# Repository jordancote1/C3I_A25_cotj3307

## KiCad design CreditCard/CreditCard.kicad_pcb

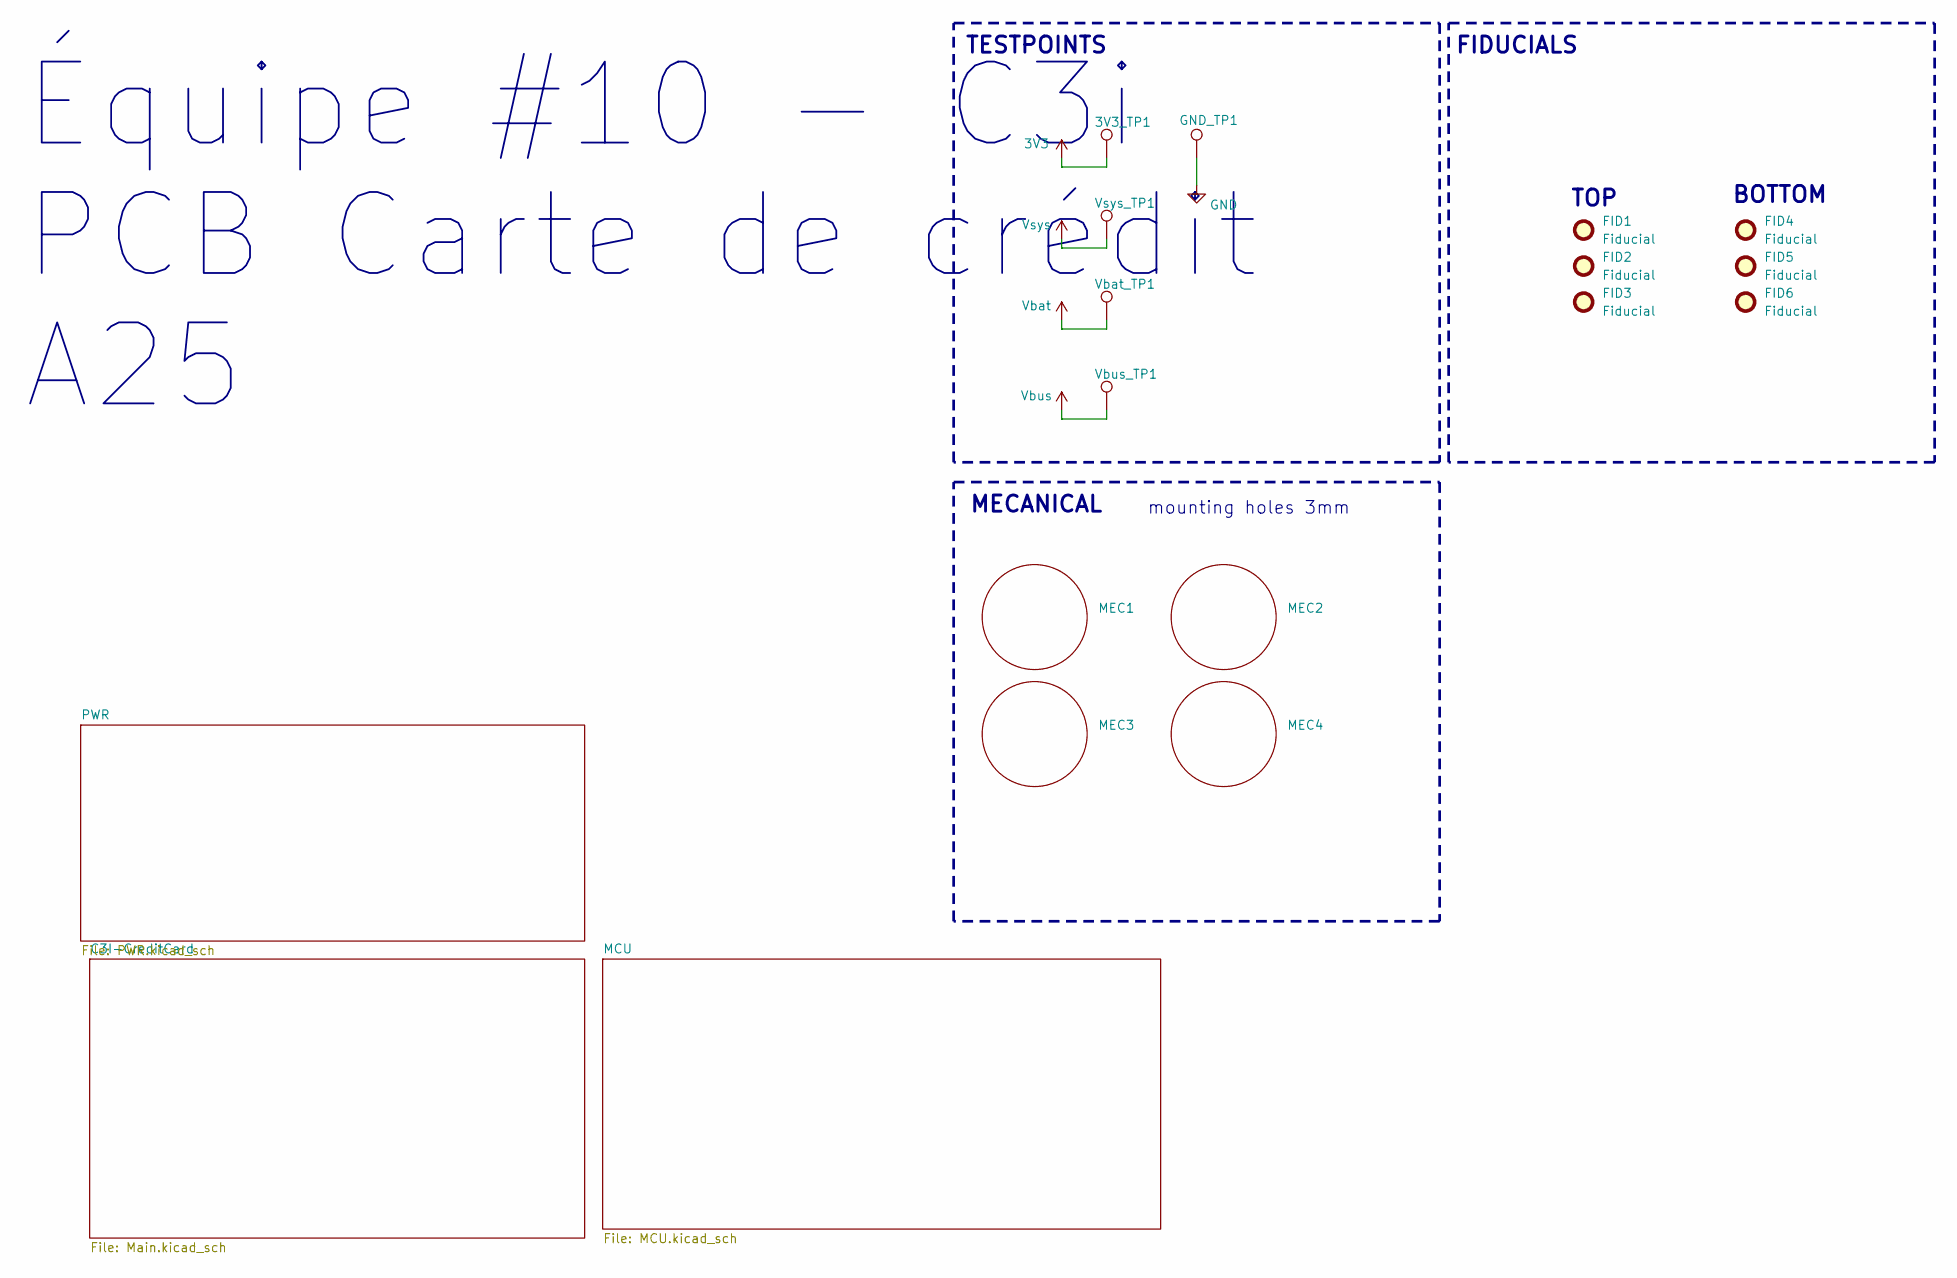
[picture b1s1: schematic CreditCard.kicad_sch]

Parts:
3V3_TP1: TP; TestPoint_Pad_D1.5mm
FID1, FID2, FID3, FID4, FID5, FID6: Fiducial; Fiducial_0.5mm_Mask1.5mm
GND_TP1: TP; TestPoint_Pad_D1.5mm
MEC1, MEC2, MEC3, MEC4: Mounting_3mm
Vbat_TP1: TP; TestPoint_Pad_D1.5mm
Vbus_TP1: TP; TestPoint_Pad_D1.5mm
Vsys_TP1: TP; TestPoint_Pad_D1.5mm

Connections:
3V3: 3V3_TP1.1; also elsewhere on the board
GND: GND_TP1.1; also elsewhere on the board
Vbat: Vbat_TP1.1; also elsewhere on the board
Vbus: Vbus_TP1.1; also elsewhere on the board
Vsys: Vsys_TP1.1; also elsewhere on the board

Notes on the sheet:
Équipe #10 - C3i PCB Carte de crédit A25
BOTTOM
MECANICAL
TESTPOINTS
FIDUCIALS
TOP
mounting holes 3mm

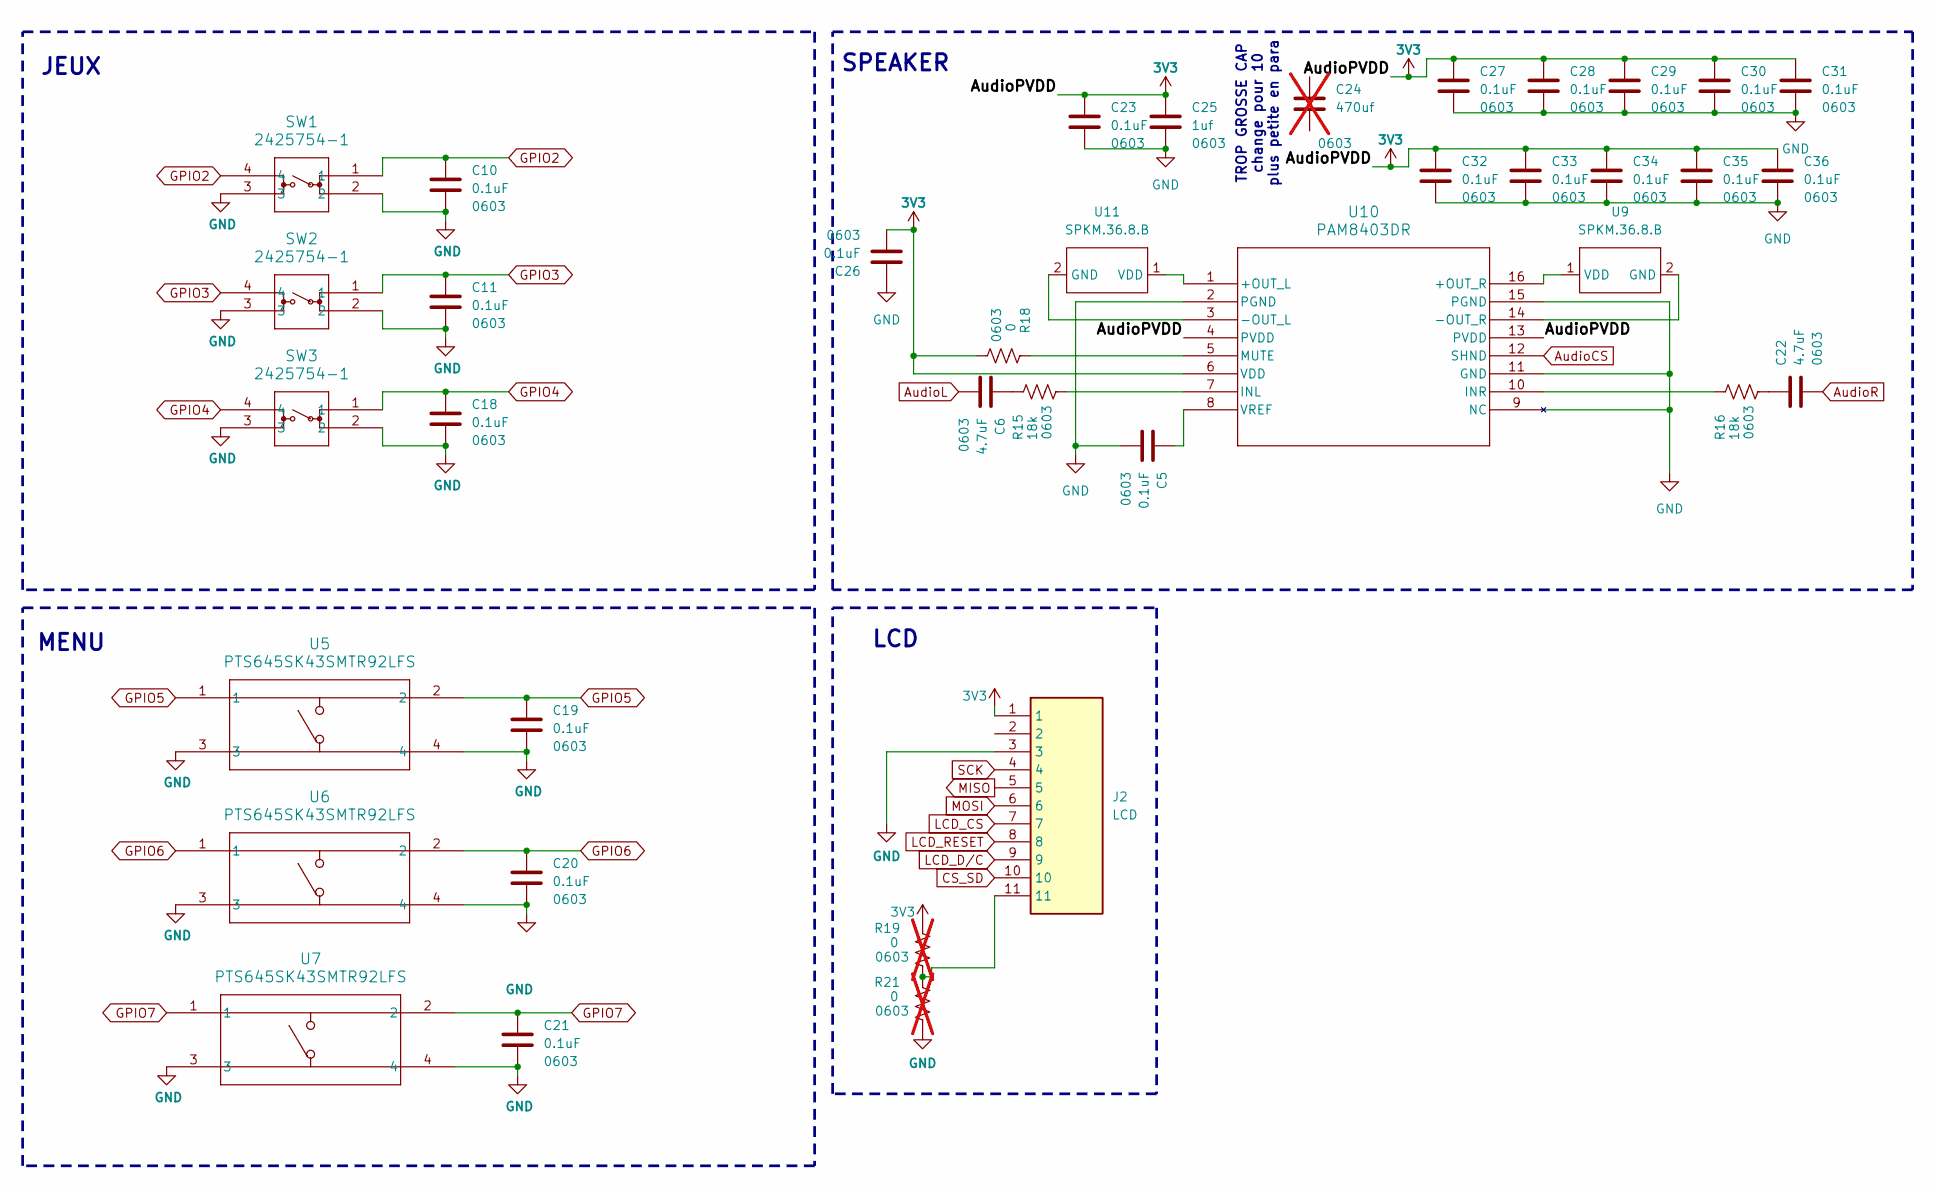
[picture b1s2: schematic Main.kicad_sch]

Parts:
C5, C10, C11, C18, C19, C20, C21, C23, C26, C27, C28, C29, C30, C31, C32, C33, C34, C35, C36: 0.1uF; C_0603_1608Metric
C6, C22: 4.7uF; C_0603_1608Metric
C24: 470uf; C_0603_1608Metric; not fitted
C25: 1uf; C_0603_1608Metric
J2: LCD; Manufacturer_Part_Number PH1-11-UA
R15, R16: 18k; R_0603_1608Metric
R18: 0; R_0603_1608Metric
R19, R21: 0; R_0603_1608Metric; not fitted
SW1, SW2, SW3: 2425754-1; 2425754-1_TEC
U5, U6, U7: PTS645SK43SMTR92LFS; SWITCH_45SK43SMTR92LFS
U9, U11: SPKM.36.8.B; SPEAKER
U10: PAM8403DR; SOIC_8403DR_DIO

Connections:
3V3: C23.1, C25.1, C26.2, C27.1, C28.1, C29.1, C30.1, C31.1, C32.1, C33.1, C34.1, C35.1, C36.1, J2.1, R18.1, R19.2, U10.4 (PVDD), U10.6 (VDD), U10.13 (PVDD); also elsewhere on the board
AudioCS: U10.12 (SHND); also elsewhere on the board
AudioL: C6.2; also elsewhere on the board
AudioR: C22.2; also elsewhere on the board
CS_SD: J2.10; also elsewhere on the board
GND: C5.2, C10.2, C11.2, C18.2, C19.2, C20.2, C21.2, C23.2, C25.2, C26.1, C27.2, C28.2, C29.2, C30.2, C31.2, C32.2, C33.2, C34.2, C35.2, C36.2, J2.3, R21.1, SW1.2, SW1.3, SW2.2, SW2.3, SW3.2, SW3.3, U5.3, U5.4, U6.3, U6.4, U7.3, U7.4, U10.2 (PGND), U10.9 (NC), U10.11 (GND), U10.15 (PGND); also elsewhere on the board
GPIO2: C10.1, SW1.1, SW1.4; also elsewhere on the board
GPIO3: C11.1, SW2.1, SW2.4; also elsewhere on the board
GPIO4: C18.1, SW3.1, SW3.4; also elsewhere on the board
GPIO5: C19.1, U5.1, U5.2; also elsewhere on the board
GPIO6: C20.1, U6.1, U6.2; also elsewhere on the board
GPIO7: C21.1, U7.1, U7.2; also elsewhere on the board
LCD_CS: J2.7; also elsewhere on the board
LCD_D/C: J2.9; also elsewhere on the board
LCD_RESET: J2.8; also elsewhere on the board
MISO: J2.5; also elsewhere on the board
MOSI: J2.6; also elsewhere on the board
unnamed: C6.1, R15.2
unnamed: C22.1, R16.1
unnamed: J2.11, R19.1, R21.2
unnamed: U10.1 (+OUT_L), U11.1 (VDD)
unnamed: U9.1 (VDD), U10.16 (+OUT_R)
unnamed: U10.3 (-OUT_L), U11.2 (GND)
unnamed: U9.2 (GND), U10.14 (-OUT_R)
unnamed: R15.1, U10.7 (INL)
unnamed: R16.2, U10.10 (INR)
unnamed: R18.2, U10.5 (MUTE)
unnamed: C5.1, U10.8 (VREF)
SCK: J2.4; also elsewhere on the board

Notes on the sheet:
JEUX
TROP GROSSE CAP change pour 10 plus petite en para
LCD
SPEAKER
MENU

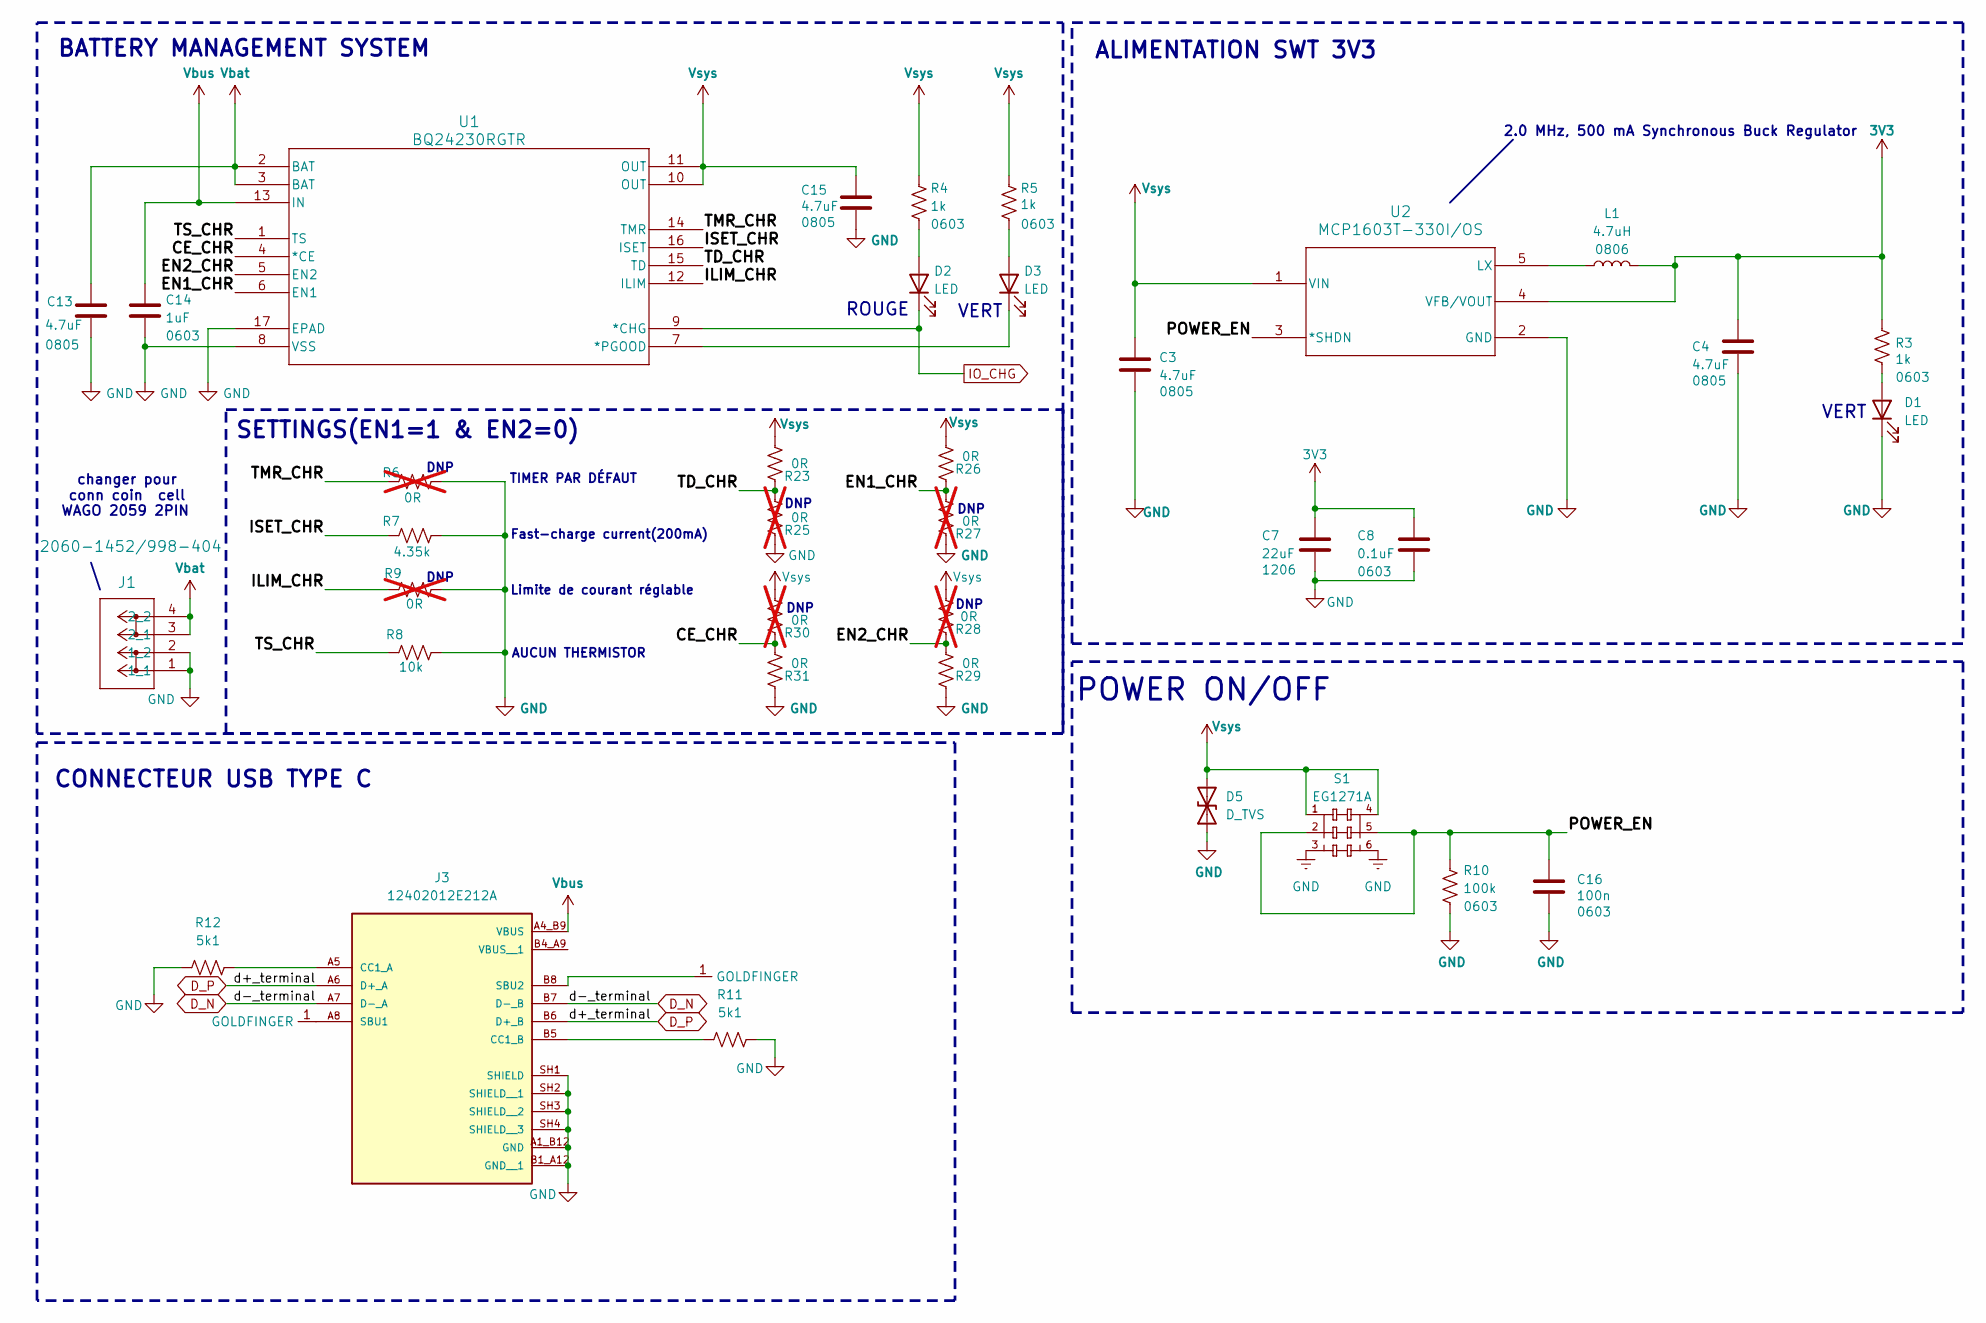
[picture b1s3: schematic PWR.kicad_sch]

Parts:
C3, C4, C13, C15: 4.7uF; C_0805_2012Metric
C7: 22uF; C_1206_3216Metric
C8: 0.1uF; C_0603_1608Metric
C14: 1uF; C_0603_1608Metric
C16: 100n; C_0603_1608Metric
D1, D2, D3: LED; LED_0805_2012Metric; DIGIKEY LINK
D5: D_TVS; D_SOD-323_HandSoldering
F5, F6: GOLD_FINGERS
J1: 2060-1452/998-404; CONN2_2059-302&slash_998-403_WAG
J3: 12402012E212A; AMPHENOL_12402012E212A; PARTREV 4
L1: 4.7uH; LED_0805_2012Metric
R3, R4, R5: 1k; R_0603_1608Metric
R6, R9, R25, R27, R28, R30: 0R; R_0402_1005Metric; not fitted
R7: 4.35k; R_0402_1005Metric
R8: 10k; R_0402_1005Metric
R10: 100k; R_0603_1608Metric
R11, R12: 5k1; R_0603_1608Metric
R23, R26, R29, R31: 0R; R_0402_1005Metric
S1: EG1271A; SW_EG1271A; PARTREV E
U1: BQ24230RGTR; RGT16_1P7X1P7
U2: MCP1603T-330I/OS; TSOT5_MC_MCH

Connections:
3V3: C4.1, C7.1, C8.1, L1.2, R3.1, U2.4 (VFB/VOUT); also elsewhere on the board
/PWR/CE_CHR: R30.1, R31.2, U1.4 (*CE)
/PWR/EN1_CHR: R26.1, R27.2, U1.6 (EN1)
/PWR/EN2_CHR: R28.1, R29.2, U1.5 (EN2)
/PWR/ILIM_CHR: R9.1, U1.12 (ILIM)
/PWR/ISET_CHR: R7.1, U1.16 (ISET)
/PWR/POWER_EN: C16.1, R10.1, S1.2, S1.5, U2.3 (*SHDN)
/PWR/TD_CHR: R23.1, R25.2, U1.15 (TD)
/PWR/TMR_CHR: R6.1, U1.14 (TMR)
/PWR/TS_CHR: R8.1, U1.1 (TS)
D_N: J3.A7 (D-_A), J3.B7 (D-_B); also elsewhere on the board
D_P: J3.A6 (D+_A), J3.B6 (D+_B); also elsewhere on the board
GND: C3.2, C4.2, C7.2, C8.2, C13.2, C14.2, C15.2, C16.2, D1.1 (K), D5.1 (A1), J1.1 (1_1), J1.2 (1_2), J3.A1_B12 (GND), J3.B1_A12 (GND__1), J3.SH1 (SHIELD), J3.SH2 (SHIELD__1), J3.SH3 (SHIELD__2), J3.SH4 (SHIELD__3), R6.2, R7.2, R8.2, R9.2, R10.2, R11.2, R12.1, R25.1, R27.1, R29.1, R31.1, S1.3, S1.6, U1.8 (VSS), U1.17 (EPAD), U2.2 (GND); also elsewhere on the board
IO_CHG: D2.1 (K), U1.9 (*CHG); also elsewhere on the board
unnamed: D1.2 (A), R3.2
unnamed: D2.2 (A), R4.2
unnamed: D3.2 (A), R5.2
unnamed: D3.1 (K), U1.7 (*PGOOD)
unnamed: F5.1 (GOLDFINGER), J3.B8 (SBU2)
unnamed: F6.1 (GOLDFINGER), J3.A8 (SBU1)
unnamed: J3.A5 (CC1_A), R12.2
unnamed: J3.B5 (CC1_B), R11.1
unnamed: L1.1, U2.5 (LX)
Vbat: C13.1, J1.3 (2_1), J1.4 (2_2), U1.2 (BAT), U1.3 (BAT); also elsewhere on the board
Vbus: C14.1, J3.A4_B9 (VBUS), U1.13 (IN); also elsewhere on the board
Vsys: C3.1, C15.1, D5.2 (A2), R4.1, R5.1, R23.2, R26.2, R28.2, R30.2, S1.1, S1.4, U1.10 (OUT), U1.11 (OUT), U2.1 (VIN); also elsewhere on the board

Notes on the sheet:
Fast-charge current(200mA)
POWER ON/OFF
DNP
WAGO 2059 2PIN
AUCUN THERMISTOR
CONNECTEUR USB TYPE C
BATTERY MANAGEMENT SYSTEM
ALIMENTATION SWT 3V3
TIMER PAR DÉFAUT
VERT
changer pour conn coin cell
SETTINGS(EN1=1 & EN2=0)
ROUGE
2.0 MHz, 500 mA Synchronous Buck Regulator
Limite de courant réglable

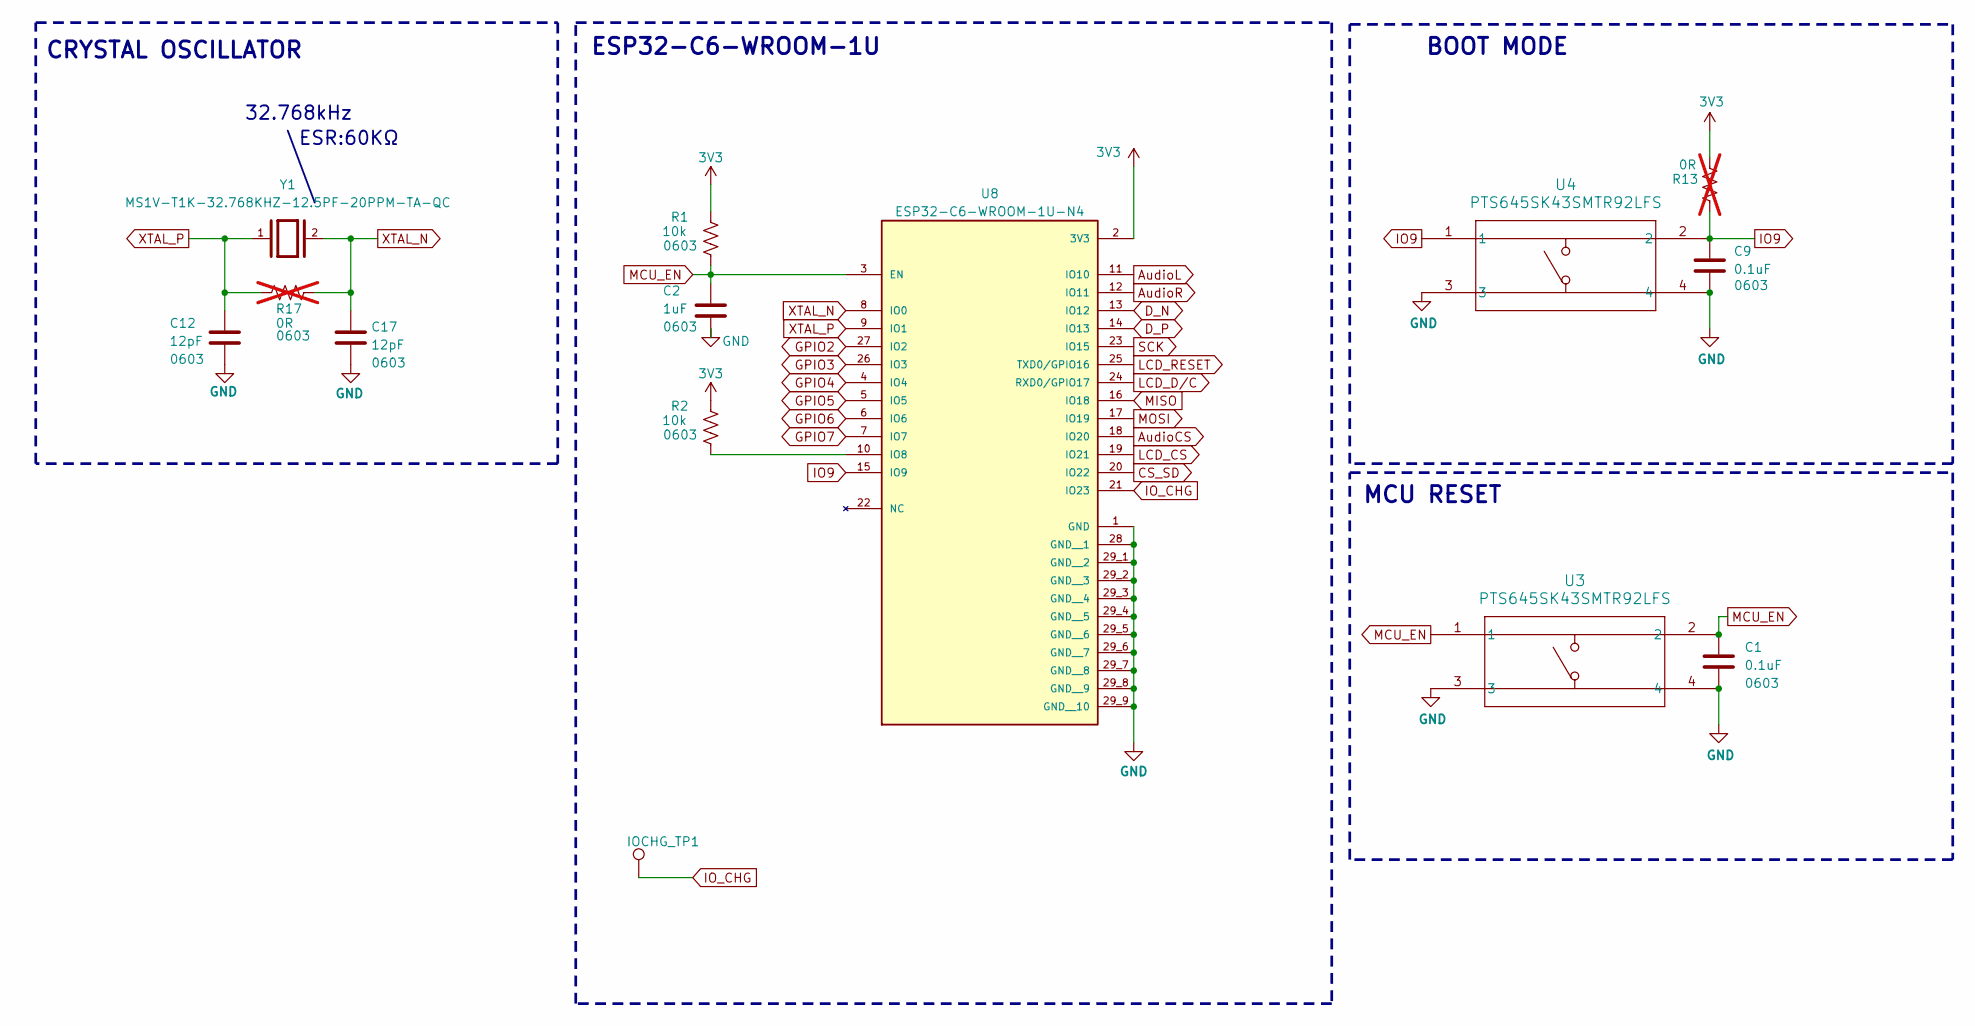
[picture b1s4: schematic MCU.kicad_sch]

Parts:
C1, C9: 0.1uF; C_0603_1608Metric
C2: 1uF; C_0603_1608Metric
C12, C17: 12pF; C_0603_1608Metric
IOCHG_TP1: TP; TestPoint_Pad_D1.5mm
R1, R2: 10k; R_0603_1608Metric
R13, R17: 0R; R_0603_1608Metric; not fitted
U3, U4: PTS645SK43SMTR92LFS; SWITCH_45SK43SMTR92LFS
U8: ESP32-C6-WROOM-1U-N4; XCVR_ESP32-C6-WROOM-1U-N4; PARTREV 1.0
Y1: MS1V-T1K-32.768KHZ-12.5PF-20PPM-TA-QC; XTAL_MS1V-T1K-32.768KHZ-12.5PF-20PPM-TA-QC; PARTREV 8.2/04.2022

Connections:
3V3: R1.2, R2.2, R13.2, U8.2 (3V3); also elsewhere on the board
AudioCS: U8.18 (IO20); also elsewhere on the board
AudioL: U8.11 (IO10); also elsewhere on the board
AudioR: U8.12 (IO11); also elsewhere on the board
CS_SD: U8.20 (IO22); also elsewhere on the board
D_N: U8.13 (IO12); also elsewhere on the board
D_P: U8.14 (IO13); also elsewhere on the board
GND: C1.2, C2.2, C9.2, C12.2, C17.2, U3.3, U3.4, U4.3, U4.4, U8.1 (GND), U8.28 (GND__1), U8.29_1 (GND__2), U8.29_2 (GND__3), U8.29_3 (GND__4), U8.29_4 (GND__5), U8.29_5 (GND__6), U8.29_6 (GND__7), U8.29_7 (GND__8), U8.29_8 (GND__9), U8.29_9 (GND__10); also elsewhere on the board
GPIO2: U8.27 (IO2); also elsewhere on the board
GPIO3: U8.26 (IO3); also elsewhere on the board
GPIO4: U8.4 (IO4); also elsewhere on the board
GPIO5: U8.5 (IO5); also elsewhere on the board
GPIO6: U8.6 (IO6); also elsewhere on the board
GPIO7: U8.7 (IO7); also elsewhere on the board
IO9: C9.1, R13.1, U4.1, U4.2, U8.15 (IO9)
IO_CHG: IOCHG_TP1.1, U8.21 (IO23); also elsewhere on the board
LCD_CS: U8.19 (IO21); also elsewhere on the board
LCD_D/C: U8.24 (RXD0/GPIO17); also elsewhere on the board
LCD_RESET: U8.25 (TXD0/GPIO16); also elsewhere on the board
MCU_EN: C1.1, C2.1, R1.1, U3.1, U3.2, U8.3 (EN)
MISO: U8.16 (IO18); also elsewhere on the board
MOSI: U8.17 (IO19); also elsewhere on the board
unnamed: R2.1, U8.10 (IO8)
SCK: U8.23 (IO15); also elsewhere on the board
XTAL_N: C17.1, R17.1, U8.8 (IO0), Y1.2
XTAL_P: C12.1, R17.2, U8.9 (IO1), Y1.1

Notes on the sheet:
CRYSTAL OSCILLATOR
32.768kHz
ESP32-C6-WROOM-1U
MCU RESET
ESR:60KΩ
BOOT MODE

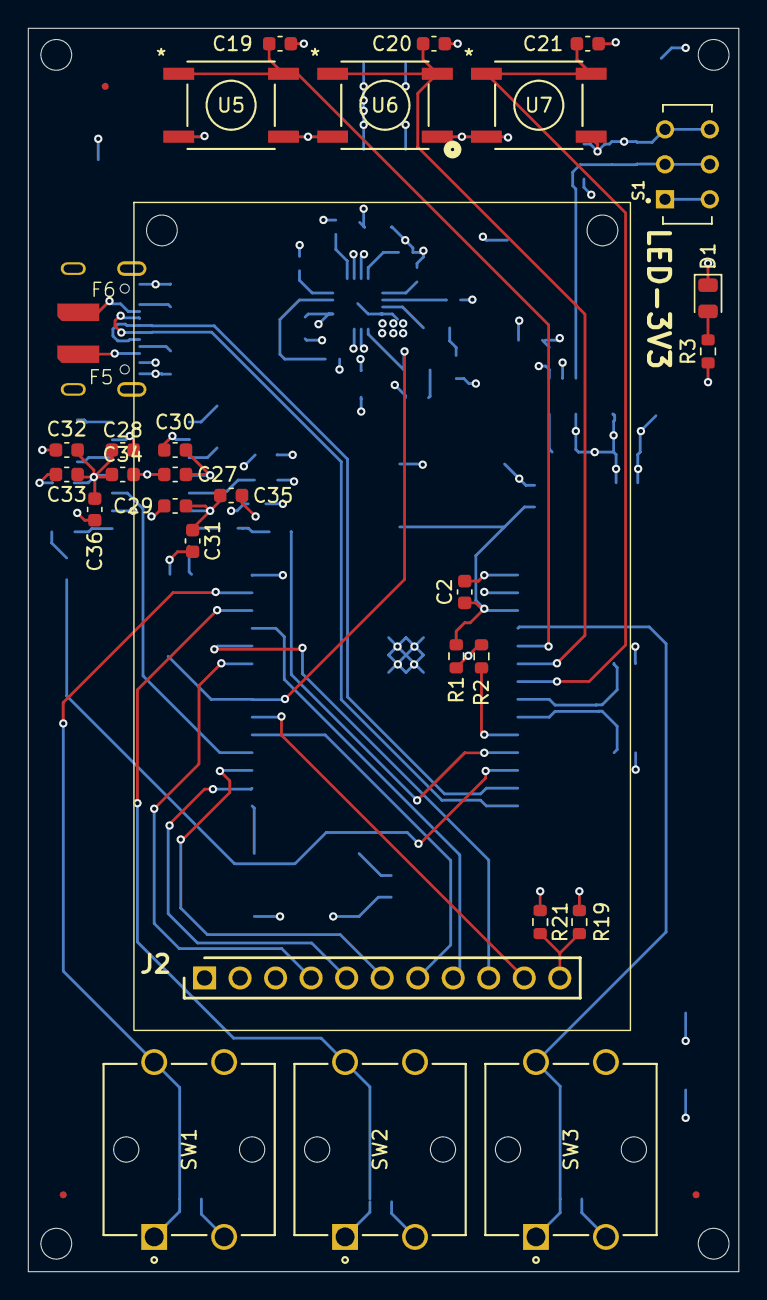
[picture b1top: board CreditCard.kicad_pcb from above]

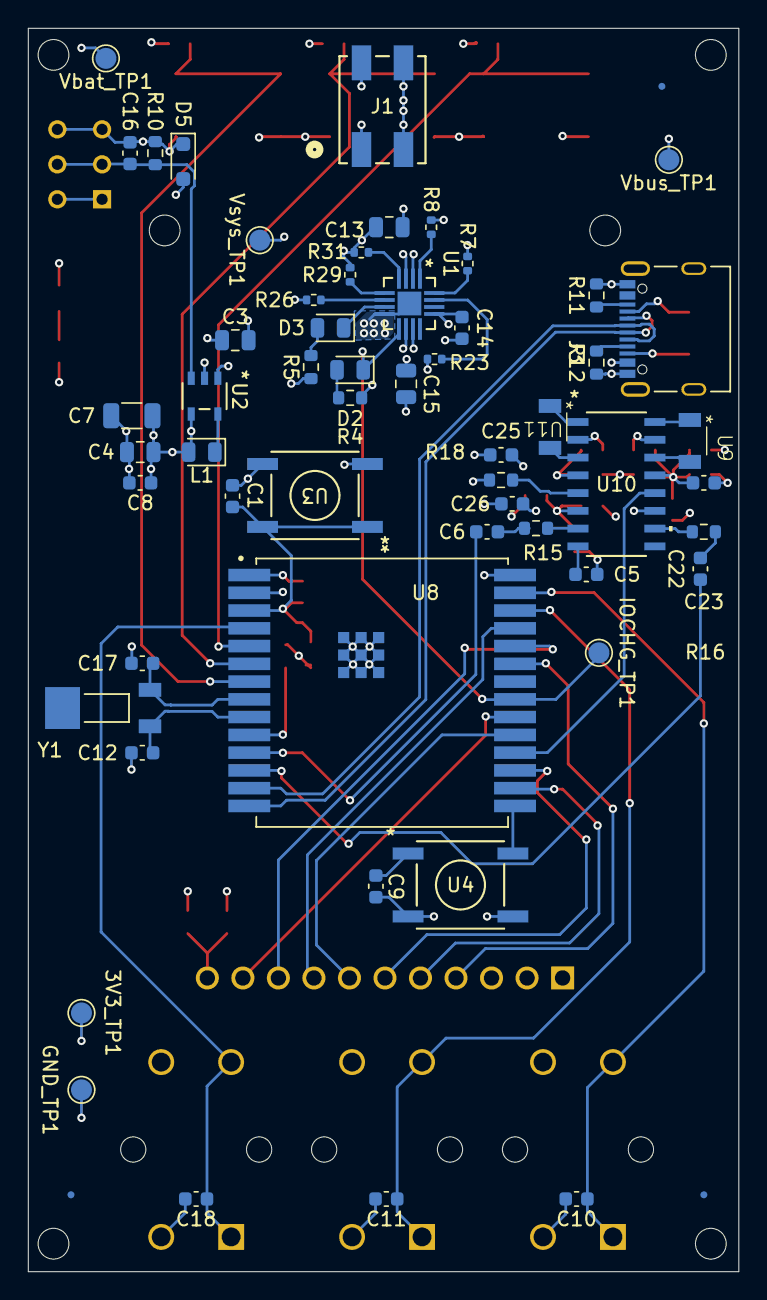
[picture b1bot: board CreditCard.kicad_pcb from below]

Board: 4 copper layers, 50.8 x 88.9 mm, 96 parts (59 on the bottom side), 56 nets.

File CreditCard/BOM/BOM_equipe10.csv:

Reference,Value,Datasheet,Footprint,Qty,DNP,Device Name
"C1,C8,C9,C16,C18",0.1uF,https://www.yageo.com/en/Chart/Download/pdf/CC0603KRX7R7BB104,Capacitor_SMD:C_0603_1608Metric,6,,CC0603KRX7R7BB104
C19,0.1uF,https://www.yageogroup.com/content/datasheet/asset/file/UPY-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,Capacitor_SMD:C_0805_2012Metric,1,,CC0805KRX7R9BB104
"C2,C14",1uF,https://www.yageogroup.com/content/datasheet/asset/file/UPY-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,Capacitor_SMD:C_0603_1608Metric,2,,CC0603KRX7R7BB105
"C3,C4,C13,C15",4.7uF,https://www.yageo.com/upload/media/product/app/datasheet/mlc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,Capacitor_SMD:C_0805_2012Metric,8,,CC0805KKX5R7BB475
C7,22uF,https://www.yageo.com/upload/media/product/app/datasheet/mlc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,Capacitor_SMD:C_1206_3216Metric,1,,CC1206KKX5R5BB226
C24,47uf,https://mm.digikey.com/Volume0/opasdata/d220001/medias/docus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,Capacitor_SMD:C_0603_1608Metric,10,,CL21A476MQYNNNE
"C12,C17",12pF,https://www.yageo.com/en/Chart/Download/pdf/CC0603JPNPO9BN120,Capacitor_SMD:C_0603_1608Metric,2,,CC0603JPNPO9BN120
D2,LED-RED,https://optoelectronics.liteon.com/upload/download/DS22-2000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,LED_SMD:LED_0805_2012Metric,1,,LTST-C171KRKT
"D1,D3",LED-GREEN,https://mm.digikey.com/Volume0/opasdata/d220001/medias/docus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,LED_SMD:LED_0805_2012Metric,2,,LTST-C171GKT
D5,D_TVS,https://www.diodes.com/assets/Datasheets/DESD5V0S1BA.pdf,Diode_SMD:D_SOD-323_HandSoldering,1,,DESD5V0S1BA-7
J1,2059-302/998-403,https://wago.priintcloud.com/datasheets/2059-302_998-403/en/,LIB:CONN2_2059-302&slash_998-403_WAG,1,,2059-302/998-403
J2,4311,https://www.digikey.ca/en/products/detail/adafruit-industrie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,Library:LCD,1,,4311
J3,12402012E212A,https://www.digikey.ca/en/products/detail/amphenol-cs-commer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,,1,,12402012E212A
L1,4.7uH,https://mm.digikey.com/Volume0/opasdata/d220001/medias/docus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,LED_SMD:LED_0805_2012Metric,1,,MBKK2012T4R7M
R8,10k,https://www.vishay.com/docs/20043/crcwhpe3.pdf,Resistor_SMD:R_0402_1005Metric,1,,CRCW040210K0FKEDHP
"R1,R2,R15",10k,https://industrial.panasonic.com/cdbs/www-data/pdf/RDM0000/A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,Resistor_SMD:R_0603_1608Metric,3,,ERJ-PB3B1002V
"R3,R4,R5,R16,R18",1k,https://www.yageogroup.com/content/datasheet/asset/file/PYU-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,Resistor_SMD:R_0603_1608Metric,5,,RC0603JR-7W1KL
R7,4.35k,https://www.yageogroup.com/content/Resource%20Library/Datash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,Resistor_SMD:R_0402_1005Metric,1,,SR0402FR-7T4K7L
R10,100k,https://www.yageogroup.com/content/datasheet/asset/file/PYU-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,Resistor_SMD:R_0603_1608Metric,1,,RC0603FR-7W100KL
"R15,R16",18k,https://www.yageogroup.com/content/datasheet/asset/file/PYU-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,Resistor_SMD:R_0603_1608Metric,2,,RC0603JR-0718KL
"R14,R20",0R,https://www.vishay.com/docs/20065/rcse3.pdf,Resistor_SMD:R_0603_1608Metric,2,,RCS06030000Z0EA
S1,EG1271A,https://www.digikey.ca/en/products/detail/e-switch/EG1271A/2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,,1,,EG1271A
U1,BQ24230RGTR,https://www.ti.com/general/docs/suppproductinfo.tsp?distId=1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,LIB:RGT16_1P7X1P7,1,,BQ24230RGTR
U2,MCP1603T-330I/OS,https://ww1.microchip.com/downloads/en/DeviceDoc/22042B.pdf,LIB:TSOT5_MC_MCH,1,,MCP1603T-330I/OS
"U3,U4,U5,U6,U7",PTS645SK43SMTR92LFS,https://www.ckswitches.com/media/1471/pts645.pdf,LIB:SWITCH_45SK43SMTR92LFS,5,,PTS645SK43SMTR92 LFS
U8,ESP32-C6-WROOM-1U-N4,https://www.espressif.com/sites/default/files/documentation/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,LIB:XCVR_ESP32-C6-WROOM-1U-N4,1,,ESP32-C6-WROOM-1U-N4
"U9,U11",SPKM.36.8.B,https://www.digikey.ca/en/products/detail/taoglas-limited/SP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,,2,,SPKM.36.8.B
U10,PAM8403DR,https://www.digikey.ca/en/products/detail/diodes-incorporate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,,1,,PAM8403DR
Y1,MS1V-T1K-32.768KHZ-12.5PF-20PPM-TA-QC,https://www.microcrystal.com/fileadmin/Media/Products/32kHz/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,LIB:XTAL_MS1V-T1K-32.768KHZ-12.5PF-20PPM-TA-QC,1,,MS1V-T1K-32.768KHZ-12.5PF-20PPM-TA-QC
N.A.,DKS-CR2032H,https://www.digikey.ca/en/products/detail/digikey/DKS-CR2032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,,1,,Coin cell holder
N.A.,CR2032,https://www.digikey.ca/en/products/detail/murata-electronics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,,1,,Coin cell battery

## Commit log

2025-10-09 Prepwork
    prep le kicad
2025-11-07 début
    début sch
2025-11-07 Premier changement
    Alice
2025-11-07 Create plan.png
    plan
2025-11-11 manque écran
    manque seulement l'écran le reste est ajouter
2025-11-11 a toi de jouer
    Manque:
    schema pour l'ampli et speaker
    rooting :)
2025-11-11 ajout des gold fingers
2025-11-11 Goldfinger
    Alice la queen
2025-11-11 debut Alice
2025-11-12 connection du audio amp
2025-11-12 ajout du LCD
2025-11-12 aliiice
2025-11-12 ajout .step usbc
2025-11-12 ajout des mounting holes 3mm
2025-11-12 aliiice fin de journée
2025-11-12 rooting presque fini
2025-11-12 Alice hihi
2025-11-12 continuité rooting
    add diff pair dn-dp
    add sw on-off on pcb
2025-11-13 Alice grosse avancée
    et oui!
2025-11-15 gerber crée
    pcb terminer
2025-11-15 petite retouche et bom complet
